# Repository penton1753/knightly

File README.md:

# Knightly

This repository contains the asset files and non-application source code for Knightly, an automatic chessboard product by Chessington. The board is able to detect its own state, move pieces, and detect moves by human players.

This repository contains SOLIDWORKS CAD files for the board, pieces, clock, and other components, STEP files created in KiCAD for the design of the printed circuit boards, Arduino microcontroller code for the detection of chess pieces, and our final project poster.

## Folder Structure

CAD files related to the board are available under [Solidworks CAD](<./Solidworks CAD/>). CAD files related to the detection PCBs are available under [PCB CAD](<./PCB CAD/>). Microcontroller code for the detection system is available under [STMDetection](./STMDetection/). Application code is available under [knightly-app](./knightly-app/) (separate repository).

## License

With the exception of our [poster](./Poster.pdf) and our [application code](./knightly-app/), all asset and code files in this repository are available under [CC BY-SA 4.0](https://creativecommons.org/licenses/by-sa/4.0/). See [LICENSE.txt](./LICENSE.txt) for more information.

## Credits

Knightly was created by Corey Chow, Colin Kwok, Yakov Shur, Andrew Wang, and Yanis Yankauskas at UC Santa Barbara as a mechanical engineering capstone project.

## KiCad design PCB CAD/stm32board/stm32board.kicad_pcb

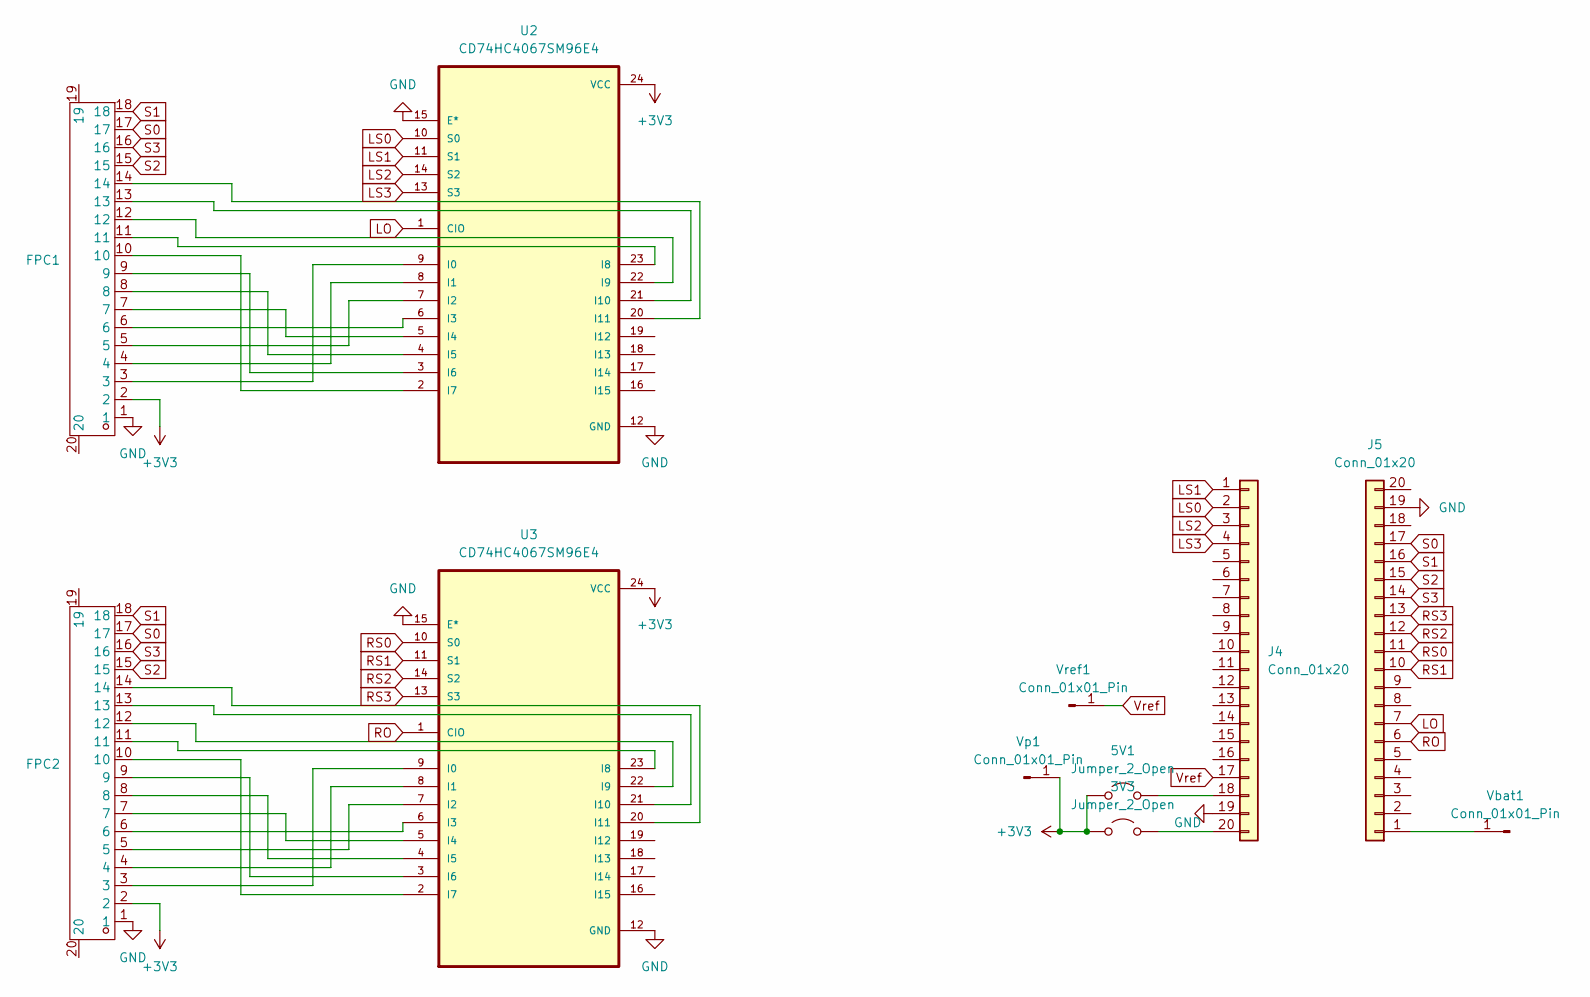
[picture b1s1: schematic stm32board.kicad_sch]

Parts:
3V3, 5V1: Jumper_2_Open; SolderJumper-2_P1.3mm_Open_RoundedPad1.0x1.5mm
FPC1, FPC2: FPC-SMD_18P-P0.50_HDGC_0.5K-HX-18PWB; Manufacturer Part 0.5K-HX-18PWB; LCSC Part Name 翻盖式 双侧触点/上下接 P数:18P 间距:0.5mm
J4, J5: Conn_01x20; PinSocket_1x20_P2.54mm_Vertical
U2, U3: CD74HC4067SM96E4; SOP65P780X200-24N; DigiKey_Part_Number 296-52634-1-ND
Vbat1: Conn_01x01_Pin; PinHeader_1x01_P2.54mm_Vertical
Vp1: Conn_01x01_Pin; PinHeader_1x01_P2.54mm_Vertical
Vref1: Conn_01x01_Pin; PinHeader_1x01_P2.54mm_Vertical

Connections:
+3V3: 3V3.1 (A), 5V1.1 (A), FPC1.2, FPC2.2, U2.24 (VCC), U3.24 (VCC), Vp1.1
GND: FPC1.1, FPC2.1, J4.19, J5.19, U2.12 (GND), U2.15 (E*), U3.12 (GND), U3.15 (E*)
LO: J5.7, U2.1 (CIO)
LS0: J4.2, U2.10 (S0)
LS1: J4.1, U2.11 (S1)
LS2: J4.3, U2.14 (S2)
LS3: J4.4, U2.13 (S3)
unnamed: 3V3.2 (B), J4.20
unnamed: 5V1.2 (B), J4.18
unnamed: J5.1, Vbat1.1
unnamed: FPC1.3, U2.9 (I0)
unnamed: FPC1.4, U2.8 (I1)
unnamed: FPC1.5, U2.7 (I2)
unnamed: FPC1.6, U2.6 (I3)
unnamed: FPC1.7, U2.5 (I4)
unnamed: FPC1.8, U2.4 (I5)
unnamed: FPC1.9, U2.3 (I6)
unnamed: FPC1.10, U2.2 (I7)
unnamed: FPC1.11, U2.23 (I8)
unnamed: FPC1.12, U2.22 (I9)
unnamed: FPC1.13, U2.21 (I10)
unnamed: FPC1.14, U2.20 (I11)
unnamed: FPC2.3, U3.9 (I0)
unnamed: FPC2.4, U3.8 (I1)
unnamed: FPC2.5, U3.7 (I2)
unnamed: FPC2.6, U3.6 (I3)
unnamed: FPC2.7, U3.5 (I4)
unnamed: FPC2.8, U3.4 (I5)
unnamed: FPC2.9, U3.3 (I6)
unnamed: FPC2.10, U3.2 (I7)
unnamed: FPC2.11, U3.23 (I8)
unnamed: FPC2.12, U3.22 (I9)
unnamed: FPC2.13, U3.21 (I10)
unnamed: FPC2.14, U3.20 (I11)
RO: J5.6, U3.1 (CIO)
RS0: J5.11, U3.10 (S0)
RS1: J5.10, U3.11 (S1)
RS2: J5.12, U3.14 (S2)
RS3: J5.13, U3.13 (S3)
S0: FPC1.17, FPC2.17, J5.17
S1: FPC1.18, FPC2.18, J5.16
S2: FPC1.15, FPC2.15, J5.15
S3: FPC1.16, FPC2.16, J5.14
Vref: J4.17, Vref1.1

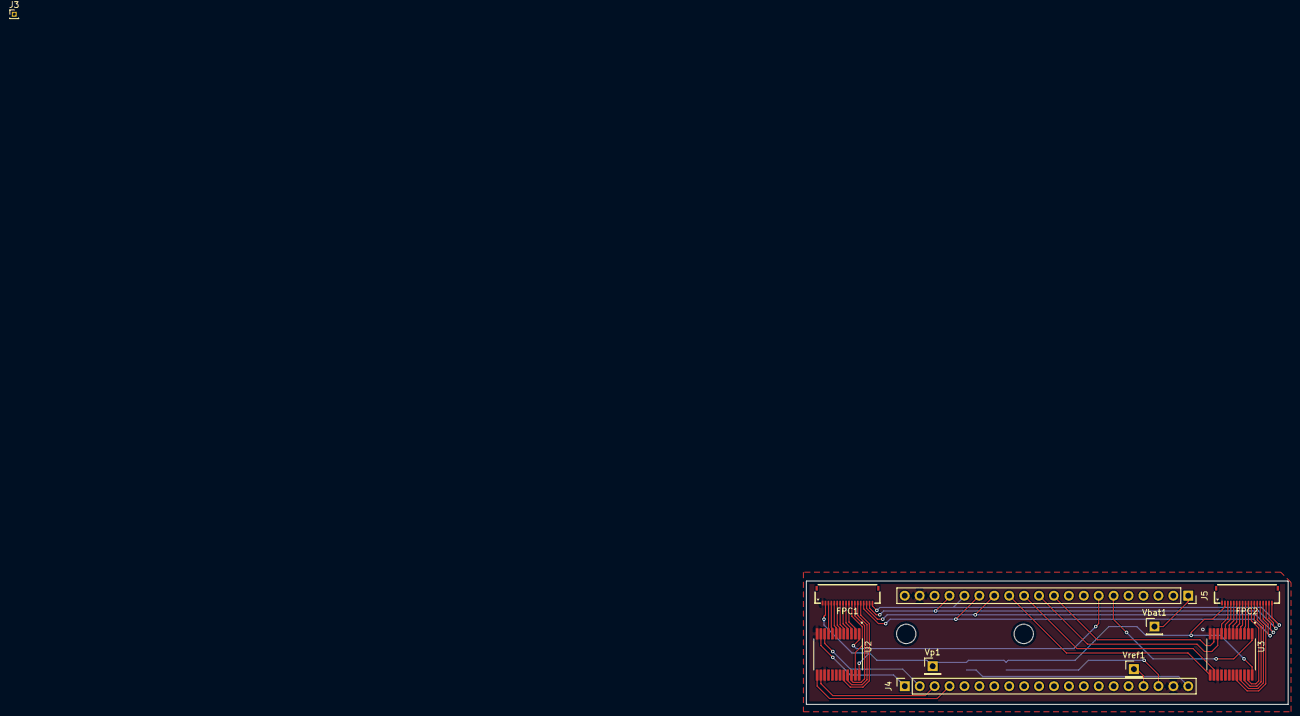
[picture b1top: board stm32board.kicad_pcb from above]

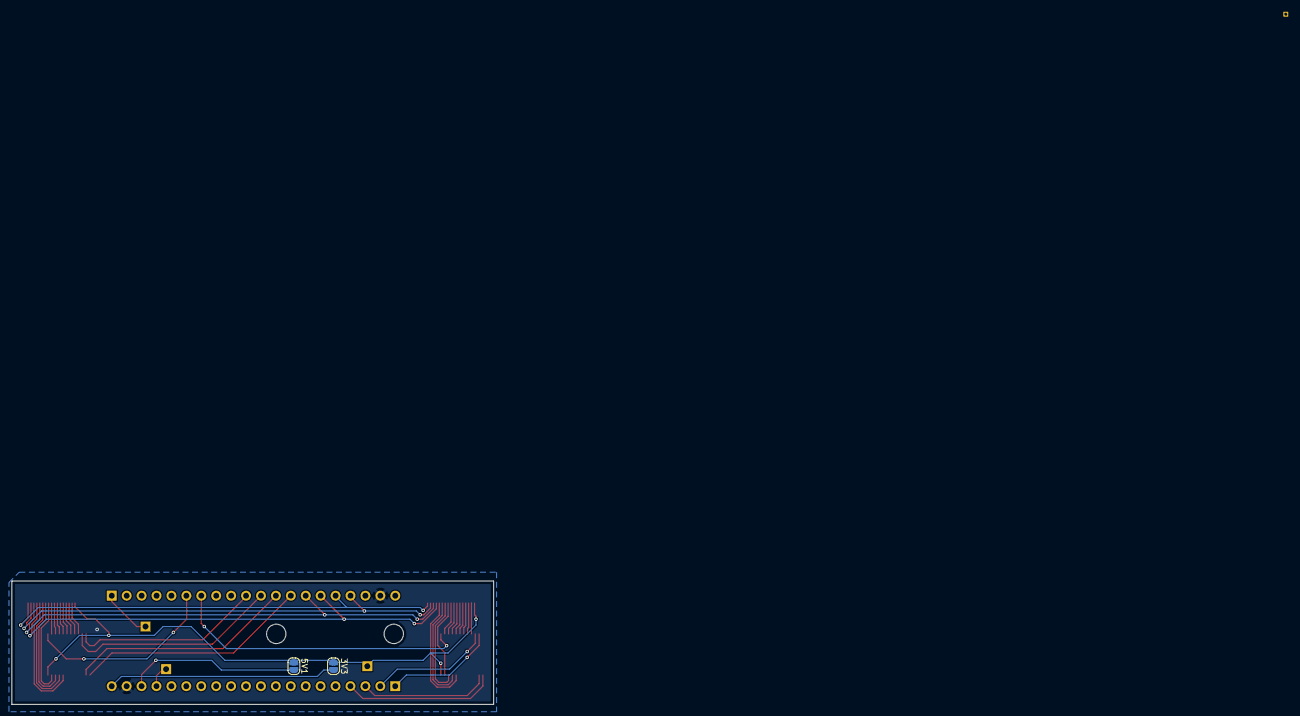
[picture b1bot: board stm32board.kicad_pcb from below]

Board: 2 copper layers, 82.0 x 21.0 mm, 12 parts (2 on the bottom side), 44 nets.

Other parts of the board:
J3: Conn_01x01_Pin; PinHeader_1x01_P1.00mm_Vertical

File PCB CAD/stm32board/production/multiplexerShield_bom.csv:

Designator,Footprint,Quantity,Value,LCSC Part #
"3V3, 5V1",SolderJumper-2_P1.3mm_Open_RoundedPad1.0x1.5mm,2,Jumper_2_Open,
"FPC1, FPC2",FPC-SMD_18P-P0.50_HDGC_0.5K-HX-18PWB,2,~,
J3,PinHeader_1x01_P1.00mm_Vertical,1,Conn_01x01_Pin,
"J4, J5",PinSocket_1x20_P2.54mm_Vertical,2,Conn_01x20,
"U2, U3",SOP65P780X200-24N,2,CD74HC4067SM96E4,
"VBAT1, VP1, VREF1",PinHeader_1x01_P2.54mm_Vertical,3,Conn_01x01_Pin,

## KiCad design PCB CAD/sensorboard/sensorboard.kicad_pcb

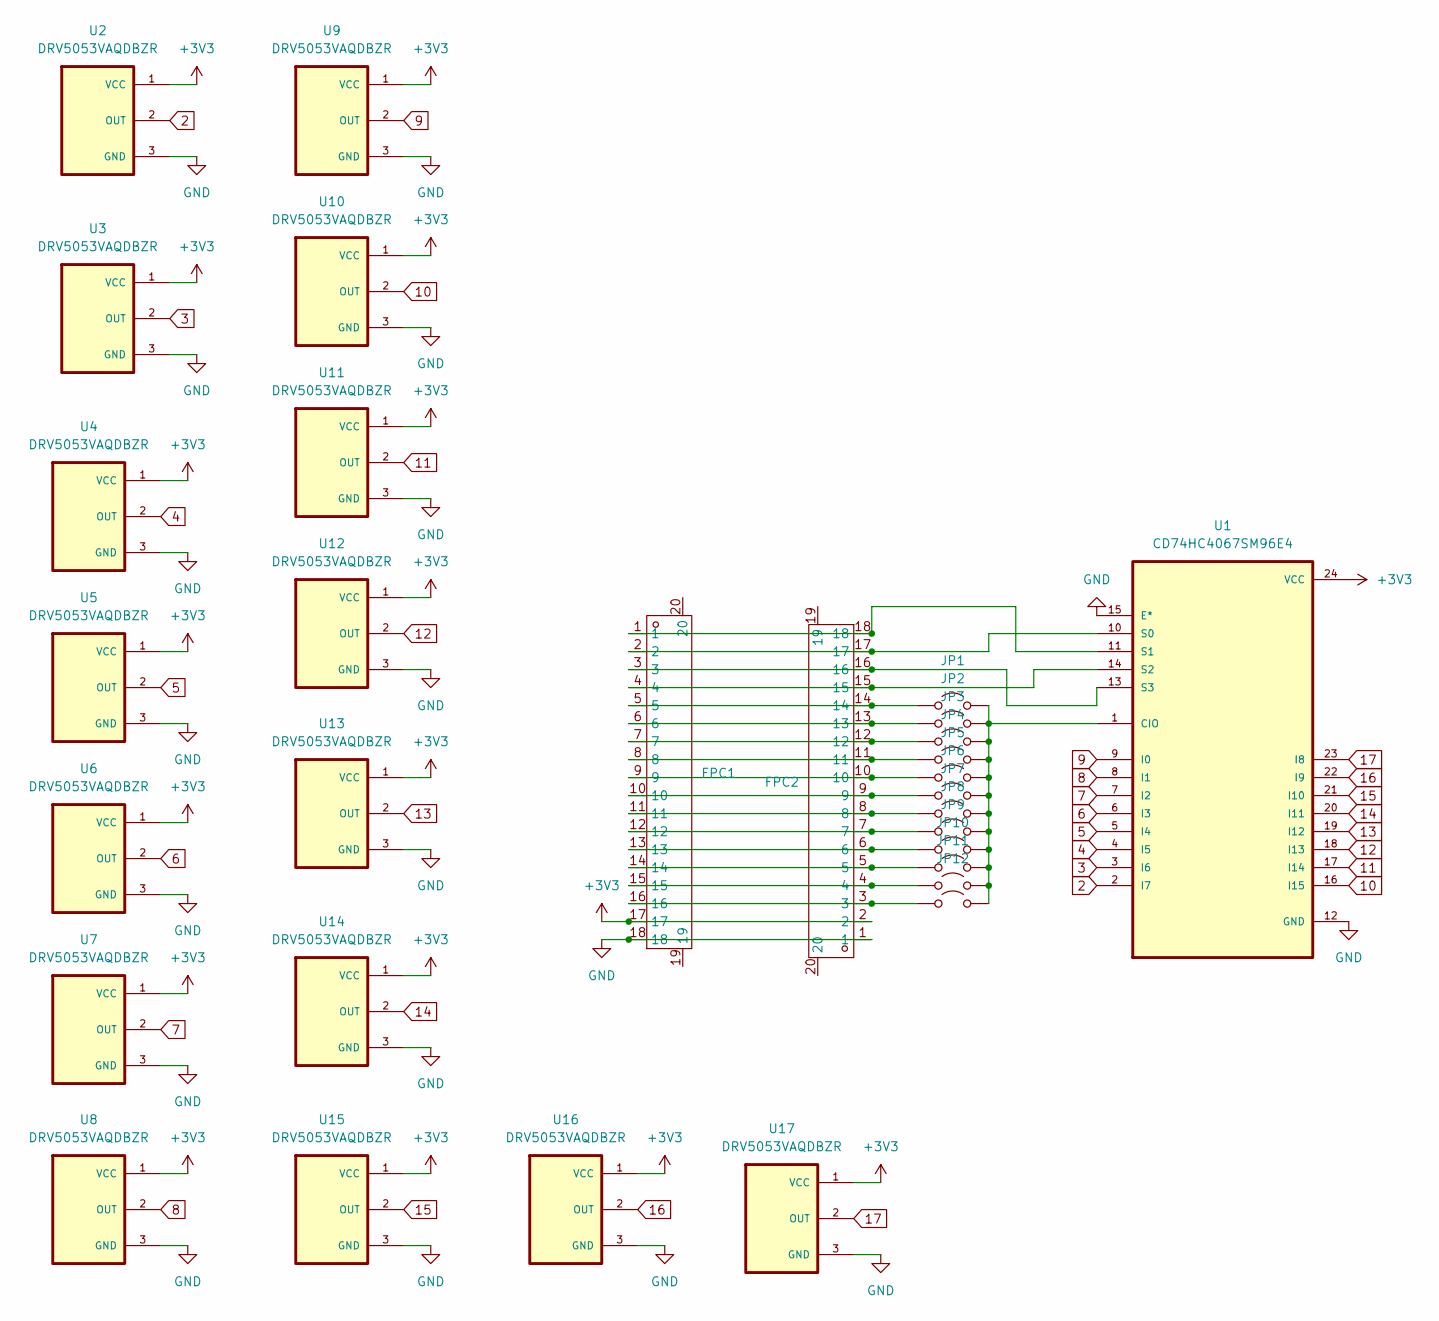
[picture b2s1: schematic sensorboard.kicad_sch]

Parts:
FPC1, FPC2: FPC-SMD_18P-P0.50_HDGC_0.5K-HX-18PWB; Manufacturer Part 0.5K-HX-18PWB; LCSC Part Name 翻盖式 双侧触点/上下接 P数:18P 间距:0.5mm
JP1, JP2, JP3, JP4, JP5, JP6, JP7, JP8, JP9, JP10, JP11, JP12: Jumper_2_Open; SolderJumper-2_P1.3mm_Open_RoundedPad1.0x1.5mm
U1: CD74HC4067SM96E4; SOP65P780X200-24N; DigiKey_Part_Number 296-52634-1-ND
U2, U3, U4, U5, U6, U7, U8, U9, U10, U11, U12, U13, U14, U15, U16, U17: DRV5053VAQDBZR; SOT95P237X112-3N; DigiKey_Part_Number 296-38460-1-ND

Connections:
2: U1.2 (I7), U2.2 (OUT)
3: U1.3 (I6), U3.2 (OUT)
4: U1.4 (I5), U4.2 (OUT)
5: U1.5 (I4), U5.2 (OUT)
6: U1.6 (I3), U6.2 (OUT)
7: U1.7 (I2), U7.2 (OUT)
8: U1.8 (I1), U8.2 (OUT)
9: U1.9 (I0), U9.2 (OUT)
10: U1.16 (I15), U10.2 (OUT)
11: U1.17 (I14), U11.2 (OUT)
12: U1.18 (I13), U12.2 (OUT)
13: U1.19 (I12), U13.2 (OUT)
14: U1.20 (I11), U14.2 (OUT)
15: U1.21 (I10), U15.2 (OUT)
16: U1.22 (I9), U16.2 (OUT)
17: U1.23 (I8), U17.2 (OUT)
+3V3: FPC1.17, FPC2.2, U1.24 (VCC), U2.1 (VCC), U3.1 (VCC), U4.1 (VCC), U5.1 (VCC), U6.1 (VCC), U7.1 (VCC), U8.1 (VCC), U9.1 (VCC), U10.1 (VCC), U11.1 (VCC), U12.1 (VCC), U13.1 (VCC), U14.1 (VCC), U15.1 (VCC), U16.1 (VCC), U17.1 (VCC)
GND: FPC1.18, FPC2.1, U1.12 (GND), U1.15 (E*), U2.3 (GND), U3.3 (GND), U4.3 (GND), U5.3 (GND), U6.3 (GND), U7.3 (GND), U8.3 (GND), U9.3 (GND), U10.3 (GND), U11.3 (GND), U12.3 (GND), U13.3 (GND), U14.3 (GND), U15.3 (GND), U16.3 (GND), U17.3 (GND)
unnamed: FPC1.5, FPC2.14, JP1.1 (A)
unnamed: JP1.2 (B), JP2.2 (B), JP3.2 (B), JP4.2 (B), JP5.2 (B), JP6.2 (B), JP7.2 (B), JP8.2 (B), JP9.2 (B), JP10.2 (B), JP11.2 (B), JP12.2 (B), U1.1 (CIO)
unnamed: FPC1.6, FPC2.13, JP2.1 (A)
unnamed: FPC1.7, FPC2.12, JP3.1 (A)
unnamed: FPC1.8, FPC2.11, JP4.1 (A)
unnamed: FPC1.9, FPC2.10, JP5.1 (A)
unnamed: FPC1.10, FPC2.9, JP6.1 (A)
unnamed: FPC1.11, FPC2.8, JP7.1 (A)
unnamed: FPC1.12, FPC2.7, JP8.1 (A)
unnamed: FPC1.13, FPC2.6, JP9.1 (A)
unnamed: FPC1.14, FPC2.5, JP10.1 (A)
unnamed: FPC1.15, FPC2.4, JP11.1 (A)
unnamed: FPC1.16, FPC2.3, JP12.1 (A)
unnamed: FPC1.2, FPC2.17, U1.10 (S0)
unnamed: FPC1.1, FPC2.18, U1.11 (S1)
unnamed: FPC1.4, FPC2.15, U1.14 (S2)
unnamed: FPC1.3, FPC2.16, U1.13 (S3)

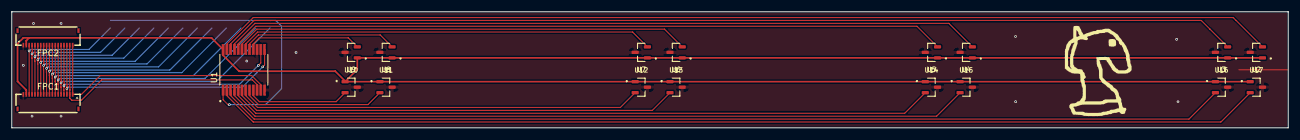
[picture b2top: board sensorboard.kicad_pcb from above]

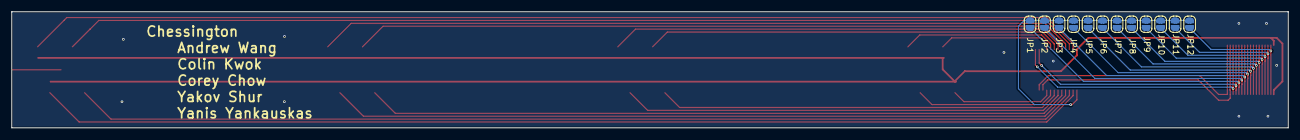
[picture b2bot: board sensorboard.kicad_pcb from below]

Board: 2 copper layers, 220.0 x 20.0 mm, 31 parts (12 on the bottom side), 35 nets.

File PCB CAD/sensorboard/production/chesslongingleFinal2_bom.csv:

Designator,Footprint,Quantity,Value,LCSC Part #
"FPC1, FPC2",FPC-SMD_18P-P0.50_HDGC_0.5K-HX-18PWB,2,~,
"JP1, JP10, JP11, JP12, JP2, JP3, JP4, JP5, JP6, JP7, JP8, JP9",SolderJumper-2_P1.3mm_Open_RoundedPad1.0x1.5mm,12,Jumper_2_Open,
U1,SOP65P780X200-24N,1,CD74HC4067SM96E4,
"U10, U11, U12, U13, U14, U15, U16, U17, U2, U3, U4, U5, U6, U7, U8, U9",SOT95P237X112-3N,16,DRV5053VAQDBZR,
